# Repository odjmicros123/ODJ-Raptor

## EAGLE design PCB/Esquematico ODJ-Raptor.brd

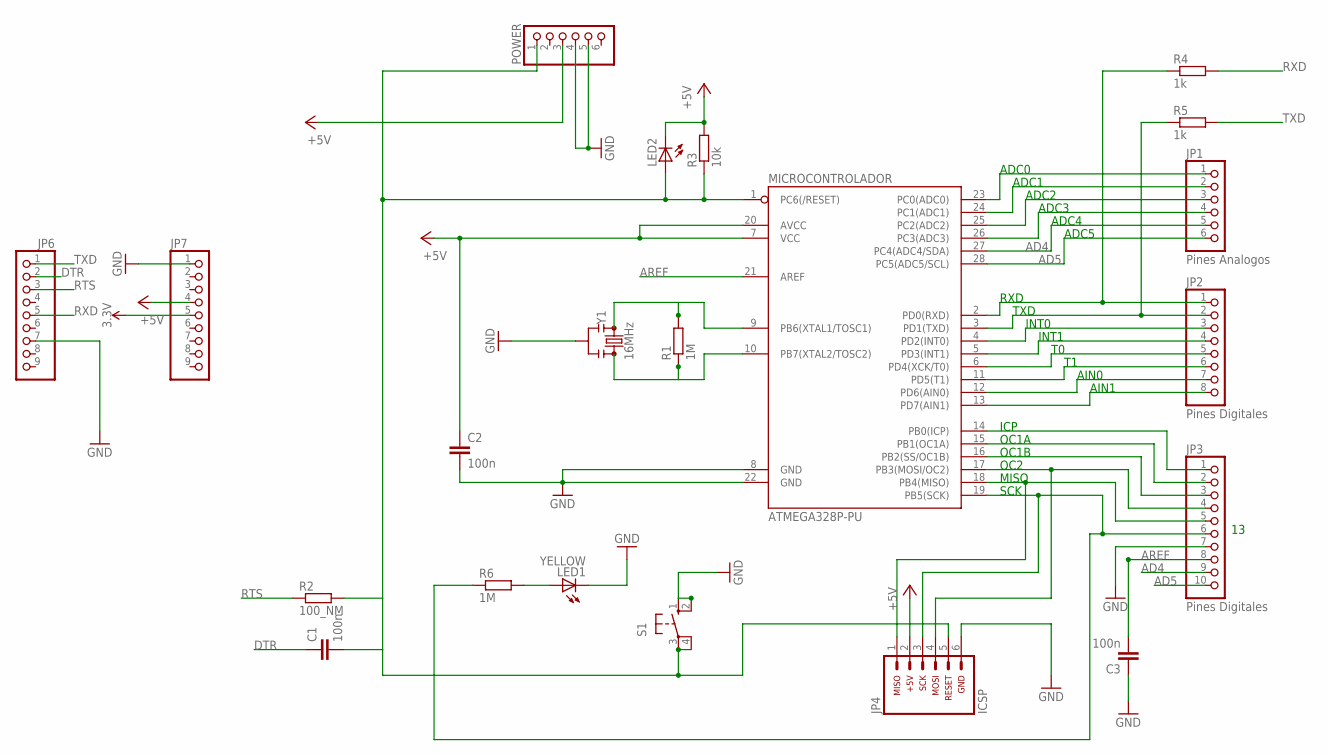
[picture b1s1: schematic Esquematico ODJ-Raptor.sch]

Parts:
C1, C2, C3: 100n; C2.5-2
JP1: Pines Analogos; 1X06
JP2: Pines Digitales; 1X08
JP3: Pines Digitales; 1X10
JP4: ARDUINO_CONN-ICSP; CONN-2X03
JP6, JP7: PINHD-1X9; 1X09-BIG
LED1: YELLOW; SMARTLED-TTW
LED2: LED; SMARTLED-TTW
MICROCONTROLADOR: ATMEGA328P-PU; DIP28
POWER: PINHD-1X6; 1X06
R1, R6: 1M; 0204/7
R2: 100_NM; 0204/7
R3: 10k; 0204/7
R4, R5: 1k; 0204/7
S1: 10-XX; B3F-10XX
Y1: 16MHz; RESONATOR-SMD-3.2X1.3

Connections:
3.3V: JP7.5
+5V: C2.1, JP4.2, JP7.4, LED2.C@1 (C), MICROCONTROLADOR.7 (VCC), MICROCONTROLADOR.20 (AVCC), POWER.3, R3.2
AD4: JP1.5, JP3.9, MICROCONTROLADOR.27 (PC4(ADC4/SDA))
AD5: JP1.6, JP3.10, MICROCONTROLADOR.28 (PC5(ADC5/SCL))
AREF: C3.2, JP3.8, MICROCONTROLADOR.21 (AREF)
DTR: C1.1, JP6.2
GND: C2.2, C3.1, JP3.7, JP4.6, JP6.7, JP7.1, LED1.C@1 (C), MICROCONTROLADOR.8 (GND), MICROCONTROLADOR.22 (GND), POWER.4, POWER.5, S1.1 (S), S1.2 (S1), Y1.2
unnamed: JP1.1, MICROCONTROLADOR.23 (PC0(ADC0))
unnamed: JP1.2, MICROCONTROLADOR.24 (PC1(ADC1))
unnamed: JP1.3, MICROCONTROLADOR.25 (PC2(ADC2))
unnamed: JP1.4, MICROCONTROLADOR.26 (PC3(ADC3))
unnamed: JP2.1, MICROCONTROLADOR.2 (PD0(RXD)), R4.1
unnamed: JP2.2, MICROCONTROLADOR.3 (PD1(TXD)), R5.1
unnamed: JP2.3, MICROCONTROLADOR.4 (PD2(INT0))
unnamed: JP2.4, MICROCONTROLADOR.5 (PD3(INT1))
unnamed: JP2.5, MICROCONTROLADOR.6 (PD4(XCK/T0))
unnamed: JP2.6, MICROCONTROLADOR.11 (PD5(T1))
unnamed: JP2.7, MICROCONTROLADOR.12 (PD6(AIN0))
unnamed: JP2.8, MICROCONTROLADOR.13 (PD7(AIN1))
unnamed: JP3.1, MICROCONTROLADOR.14 (PB0(ICP))
unnamed: JP3.2, MICROCONTROLADOR.15 (PB1(OC1A))
unnamed: JP3.3, MICROCONTROLADOR.16 (PB2(SS/OC1B))
unnamed: JP3.4, JP4.4, MICROCONTROLADOR.17 (PB3(MOSI/OC2))
unnamed: JP3.5, JP4.1, MICROCONTROLADOR.18 (PB4(MISO))
unnamed: JP3.6, JP4.3, MICROCONTROLADOR.19 (PB5(SCK)), R6.1
unnamed: MICROCONTROLADOR.9 (PB6(XTAL1/TOSC1)), R1.2, Y1.1
unnamed: MICROCONTROLADOR.10 (PB7(XTAL2/TOSC2)), R1.1, Y1.3
unnamed: C1.2, JP4.5, LED2.A@1 (A), MICROCONTROLADOR.1 (PC6(/RESET)), POWER.1, R2.2, R3.1, S1.3, S1.4 (P1)
unnamed: LED1.A@1 (A), R6.2
RTS: JP6.3, R2.1
RXD: JP6.5, R4.2
TXD: JP6.1, R5.2

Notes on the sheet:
ADC0
ADC1
ADC2
ADC3
ADC4
ADC5
ICP
OC1A
OC1B
OC2
MISO
SCK
RXD
TXD
INT0
INT1
AIN0
AIN1

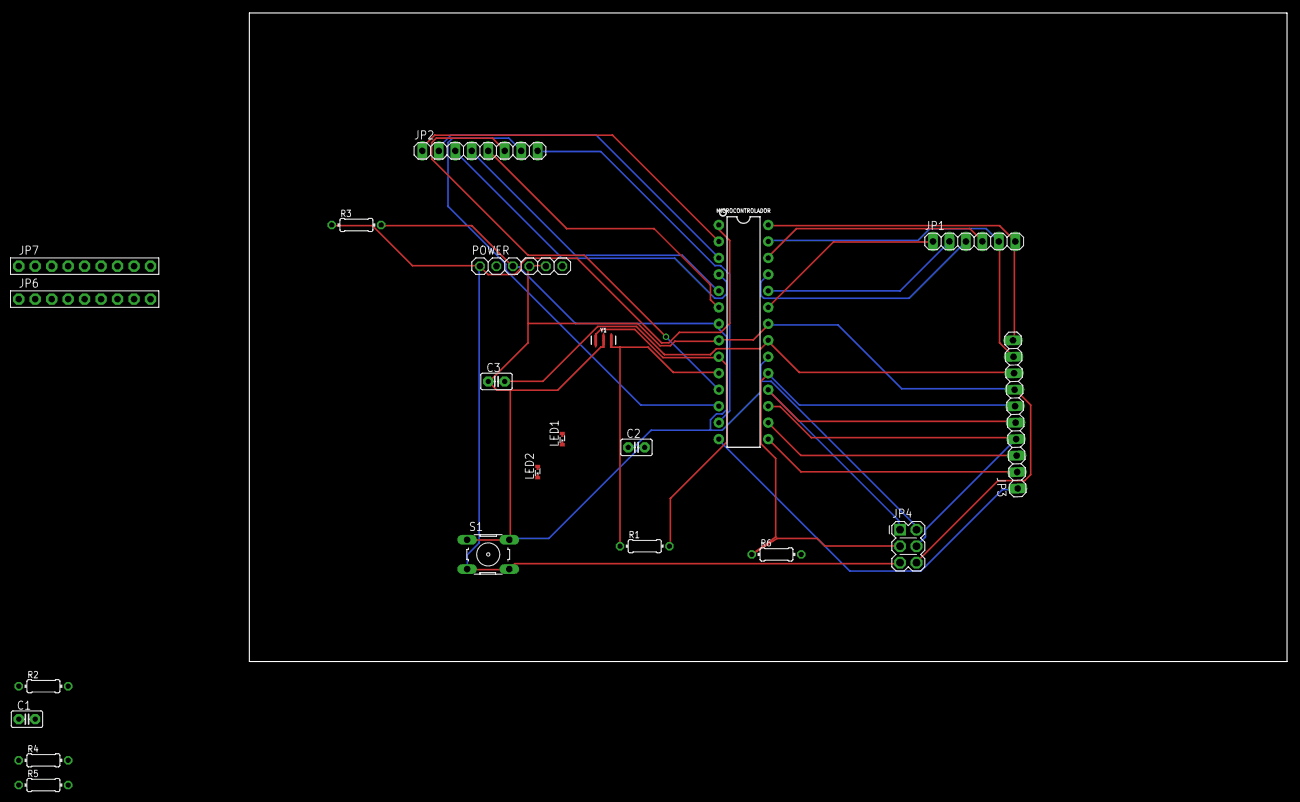
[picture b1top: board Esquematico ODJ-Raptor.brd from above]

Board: 2 copper layers, 160.0 x 100.0 mm, 21 parts (0 on the bottom side), 31 nets.

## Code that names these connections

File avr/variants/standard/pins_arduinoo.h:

/*
  pins_arduino.h - Pin definition functions for Arduino
  Part of Arduino - http://www.arduino.cc/

  Copyright (c) 2007 David A. Mellis

  This library is free software; you can redistribute it and/or
  modify it under the terms of the GNU Lesser General Public
  License as published by the Free Software Foundation; either
  version 2.1 of the License, or (at your option) any later version.

  This library is distributed in the hope that it will be useful,
  but WITHOUT ANY WARRANTY; without even the implied warranty of
  MERCHANTABILITY or FITNESS FOR A PARTICULAR PURPOSE.  See the GNU
  Lesser General Public License for more details.

  You should have received a copy of the GNU Lesser General
  Public License along with this library; if not, write to the
  Free Software Foundation, Inc., 59 Temple Place, Suite 330,
  Boston, MA  02111-1307  USA
*/

#ifndef Pins_Arduino_h
#define Pins_Arduino_h

#include <avr/pgmspace.h>

#define NUM_DIGITAL_PINS            20
#define NUM_ANALOG_INPUTS           6
#define analogInputToDigitalPin(p)  ((p < 6) ? (p) + 14 : -1)

#if defined(__AVR_ATmega8__)
#define digitalPinHasPWM(p)         ((p) == 9 || (p) == 10 || (p) == 11)
#else
#define digitalPinHasPWM(p)         ((p) == 3 || (p) == 5 || (p) == 6 || (p) == 9 || (p) == 10 || (p) == 11)
#endif

#define PIN_SPI_SS    (10)
#define PIN_SPI_MOSI  (11)
#define PIN_SPI_MISO  (12)
#define PIN_SPI_SCK   (13)

static const uint8_t SS   = PIN_SPI_SS;
static const uint8_t MOSI = PIN_SPI_MOSI;
static const uint8_t MISO = PIN_SPI_MISO;
static const uint8_t SCK  = PIN_SPI_SCK;

#define PIN_WIRE_SDA        (18)
#define PIN_WIRE_SCL        (19)

static const uint8_t SDA = PIN_WIRE_SDA;
static const uint8_t SCL = PIN_WIRE_SCL;

#define LED_BUILTIN 13

#define PIN_A0   (14)
#define PIN_A1   (15)
#define PIN_A2   (16)
#define PIN_A3   (17)
#define PIN_A4   (18)
#define PIN_A5   (19)
#define PIN_A6   (20)
#define PIN_A7   (21)

static const uint8_t A0 = PIN_A0;
static const uint8_t A1 = PIN_A1;
static const uint8_t A2 = PIN_A2;
static const uint8_t A3 = PIN_A3;
static const uint8_t A4 = PIN_A4;
static const uint8_t A5 = PIN_A5;
static const uint8_t A6 = PIN_A6;
static const uint8_t A7 = PIN_A7;

#define digitalPinToPCICR(p)    (((p) >= 0 && (p) <= 21) ? (&PCICR) : ((uint8_t *)0))
#define digitalPinToPCICRbit(p) (((p) <= 7) ? 2 : (((p) <= 13) ? 0 : 1))
#define digitalPinToPCMSK(p)    (((p) <= 7) ? (&PCMSK2) : (((p) <= 13) ? (&PCMSK0) : (((p) <= 21) ? (&PCMSK1) : ((uint8_t *)0))))
#define digitalPinToPCMSKbit(p) (((p) <= 7) ? (p) : (((p) <= 13) ? ((p) - 8) : ((p) - 14)))

#define digitalPinToInterrupt(p)  ((p) == 2 ? 0 : ((p) == 3 ? 1 : NOT_AN_INTERRUPT))

#ifdef ARDUINO_MAIN

// On the Arduino board, digital pins are also used
// for the analog output (software PWM).  Analog input
// pins are a separate set.

// ATMEL ATMEGA8 & 168 / ARDUINO
//
//                  +-\/-+
//            PC6  1|    |28  PC5 (AI 5)
//      (D 0) PD0  2|    |27  PC4 (AI 4)
//      (D 1) PD1  3|    |26  PC3 (AI 3)
//      (D 2) PD2  4|    |25  PC2 (AI 2)
// PWM+ (D 3) PD3  5|    |24  PC1 (AI 1)
//      (D 4) PD4  6|    |23  PC0 (AI 0)
//            VCC  7|    |22  GND
//            GND  8|    |21  AREF
//            PB6  9|    |20  AVCC
//            PB7 10|    |19  PB5 (D 13)
// PWM+ (D 5) PD5 11|    |18  PB4 (D 12)
// PWM+ (D 6) PD6 12|    |17  PB3 (D 11) PWM
//      (D 7) PD7 13|    |16  PB2 (D 10) PWM
//      (D 8) PB0 14|    |15  PB1 (D 9) PWM
//                  +----+
//
// (PWM+ indicates the additional PWM pins on the ATmega168.)

// ATMEL ATMEGA1280 / ARDUINO
//
// 0-7 PE0-PE7   works
// 8-13 PB0-PB5  works
// 14-21 PA0-PA7 works
// 22-29 PH0-PH7 works
// 30-35 PG5-PG0 works
// 36-43 PC7-PC0 works
// 44-51 PJ7-PJ0 works
// 52-59 PL7-PL0 works
// 60-67 PD7-PD0 works
// A0-A7 PF0-PF7
// A8-A15 PK0-PK7


// these arrays map port names (e.g. port B) to the
// appropriate addresses for various functions (e.g. reading
// and writing)
const uint16_t PROGMEM port_to_mode_PGM[] = {
	NOT_A_PORT,
	NOT_A_PORT,
	(uint16_t) &DDRB,
	(uint16_t) &DDRC,
	(uint16_t) &DDRD,
};

const uint16_t PROGMEM port_to_output_PGM[] = {
	NOT_A_PORT,
	NOT_A_PORT,
	(uint16_t) &PORTB,
	(uint16_t) &PORTC,
	(uint16_t) &PORTD,
};

const uint16_t PROGMEM port_to_input_PGM[] = {
	NOT_A_PORT,
	NOT_A_PORT,
	(uint16_t) &PINB,
	(uint16_t) &PINC,
	(uint16_t) &PIND,
};

const uint8_t PROGMEM digital_pin_to_port_PGM[] = {
	PD, /* 0 */
	PD,
	PD,
	PD,
	PD,
	PD,
	PD,
	PD,
	PB, /* 8 */
	PB,
	PB,
	PB,
	PB,
	PB,
	PC, /* 14 */
	PC,
	PC,
	PC,
	PC,
	PC,
};

const uint8_t PROGMEM digital_pin_to_bit_mask_PGM[] = {
	_BV(0), /* 0, port D */
	_BV(1),
	_BV(4),
	_BV(7),
	_BV(2),
	_BV(6),
	_BV(3),
	_BV(5),
	_BV(4), /* 8, port B */
	_BV(2),
	_BV(0),
	_BV(5),
	_BV(1),
	_BV(3),
	_BV(1), /* 14, port C */
	_BV(3),
	_BV(2),
	_BV(5),
	_BV(4),
	_BV(0),
};

const uint8_t PROGMEM digital_pin_to_timer_PGM[] = {
	NOT_ON_TIMER, /* 0 - port D */
	NOT_ON_TIMER,
	NOT_ON_TIMER,
	// on the ATmega168, digital pin 3 has hardware pwm
#if defined(__AVR_ATmega8__)
	NOT_ON_TIMER,
#else
	TIMER2B,
#endif
	NOT_ON_TIMER,
	// on the ATmega168, digital pins 5 and 6 have hardware pwm
#if defined(__AVR_ATmega8__)
	NOT_ON_TIMER,
	NOT_ON_TIMER,
#else
	TIMER0B,
	TIMER0A,
#endif
	NOT_ON_TIMER,
	NOT_ON_TIMER, /* 8 - port B */
	TIMER1A,
	TIMER1B,
#if defined(__AVR_ATmega8__)
	TIMER2,
#else
	TIMER2A,
#endif
	NOT_ON_TIMER,
	NOT_ON_TIMER,
	NOT_ON_TIMER,
	NOT_ON_TIMER, /* 14 - port C */
	NOT_ON_TIMER,
	NOT_ON_TIMER,
	NOT_ON_TIMER,
	NOT_ON_TIMER,
};

#endif

// These serial port names are intended to allow libraries and architecture-neutral
// sketches to automatically default to the correct port name for a particular type
// of use.  For example, a GPS module would normally connect to SERIAL_PORT_HARDWARE_OPEN,
// the first hardware serial port whose RX/TX pins are not dedicated to another use.
//
// SERIAL_PORT_MONITOR        Port which normally prints to the Arduino Serial Monitor
//
// SERIAL_PORT_USBVIRTUAL     Port which is USB virtual serial
//
// SERIAL_PORT_LINUXBRIDGE    Port which connects to a Linux system via Bridge library
//
// SERIAL_PORT_HARDWARE       Hardware serial port, physical RX & TX pins.
//
// SERIAL_PORT_HARDWARE_OPEN  Hardware serial ports which are open for use.  Their RX & TX
//                            pins are NOT connected to anything by default.
#define SERIAL_PORT_MONITOR   Serial
#define SERIAL_PORT_HARDWARE  Serial

#endif

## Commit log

2017-02-20 Primer Boceto del Proyecto 1
2017-02-21 Archivo json tarjeta ODJ-Raptor
2017-02-21 Agregando código del ODJ-Raptor
2017-02-21 Modificacion del codigo de la tarjeta ODJ-Raptor
2017-02-21 Modificando el código
2017-02-24 Se agregó la carpeta AVR
2017-02-24 Se agrego la carpeta AVR
2017-02-27 Modificando el archivo del pdf
2017-02-27 Eliminando PDF
2017-02-27 Agregando el PCB al repositorio
2017-02-28 v0.1.0
2017-02-28 Prueba.
2017-02-28 Agregando nueva carpeta Eagle, reemplazando la antigua PCB
2017-03-08 Agregando la foto de la baquela del Arduino.
2017-03-13 se modificaron todos los puertos

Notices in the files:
parts and their libraries:
SparkFun-IC-Microcontroller: Licensing: Creative Commons ShareAlike 4.0 International - https://creativecommons.org/licenses/by-sa/4.0
